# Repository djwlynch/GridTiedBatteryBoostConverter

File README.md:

# GridTiedBatteryBoostConverter

This is a project to build a device that will allow a 28 Cell 100AH LiFePo4 Battery Pack
to be connected to a generic MPPT Grid Tied Inverter via the solar DC input.
It will limit the power drawn from the battery pack to a maximum of 1000W.
This should allow a good base load for a typical 1st world house.
The LiFePo4 cell is 3.2V nominal voltage and 3.65V Max. 3.1V is fairly flat,so
this means the 28 cell battery pack voltage range should be 86.8V min 89.6V Nominal and 102.2V Max.
The majority of Grid tied inverters I have seen won't start until they get 150V DC from Pannels,
so this device will boost this voltage up to 160V.  It will include a current sense transformer and
isolating transformer to sample the house Voltage and current Draw, and thus be able to determine the
houses power consumption from the Grid.  It will be able to sense the power that it is supplying
to the Grid Tied inverter, and use this info to try to keep the house power from the Grid at about 0 Watts.
It will do this until it supplies a maximum of 1000W to the inverter, any higher than this and the grid
can supply it.  It will also have FETs for turning on and off a seperate charger.
The charger is 2000W 102.2V 20A. The CPU of the system is a Teensy_LC, with LCD, 3 buttons and a ESP_WROOM_02U
wifi module. The LCD is driven by an I2C bus the ESP has jumperable access to this bus also, and the I2C
bus is brought out to a header incase extra monitoring is required ie temperature or pressure etc.

The peak current mode control is based around the UCC2800 TI mosfet gate driver.

Warning I am not an electrical engineer and this may kill you / burn down your house,
all risks are your own.  I have not yet built this myself, but will update when I have.

<b>To install :</b>
change into your kicad projects directory and issue<br>
git clone https://github.com/djwlynch/GridTiedBatteryBoostConverter
Also in you kicad project directory issue the following<br>
git clone https://github.com/djwlynch/custom_kicad_library --recursive

the --recursive is important and it pulls down the required submodules for kicad librarys I have used,
namely teensy_library and teensy.pretty and digikey_kicad_library.

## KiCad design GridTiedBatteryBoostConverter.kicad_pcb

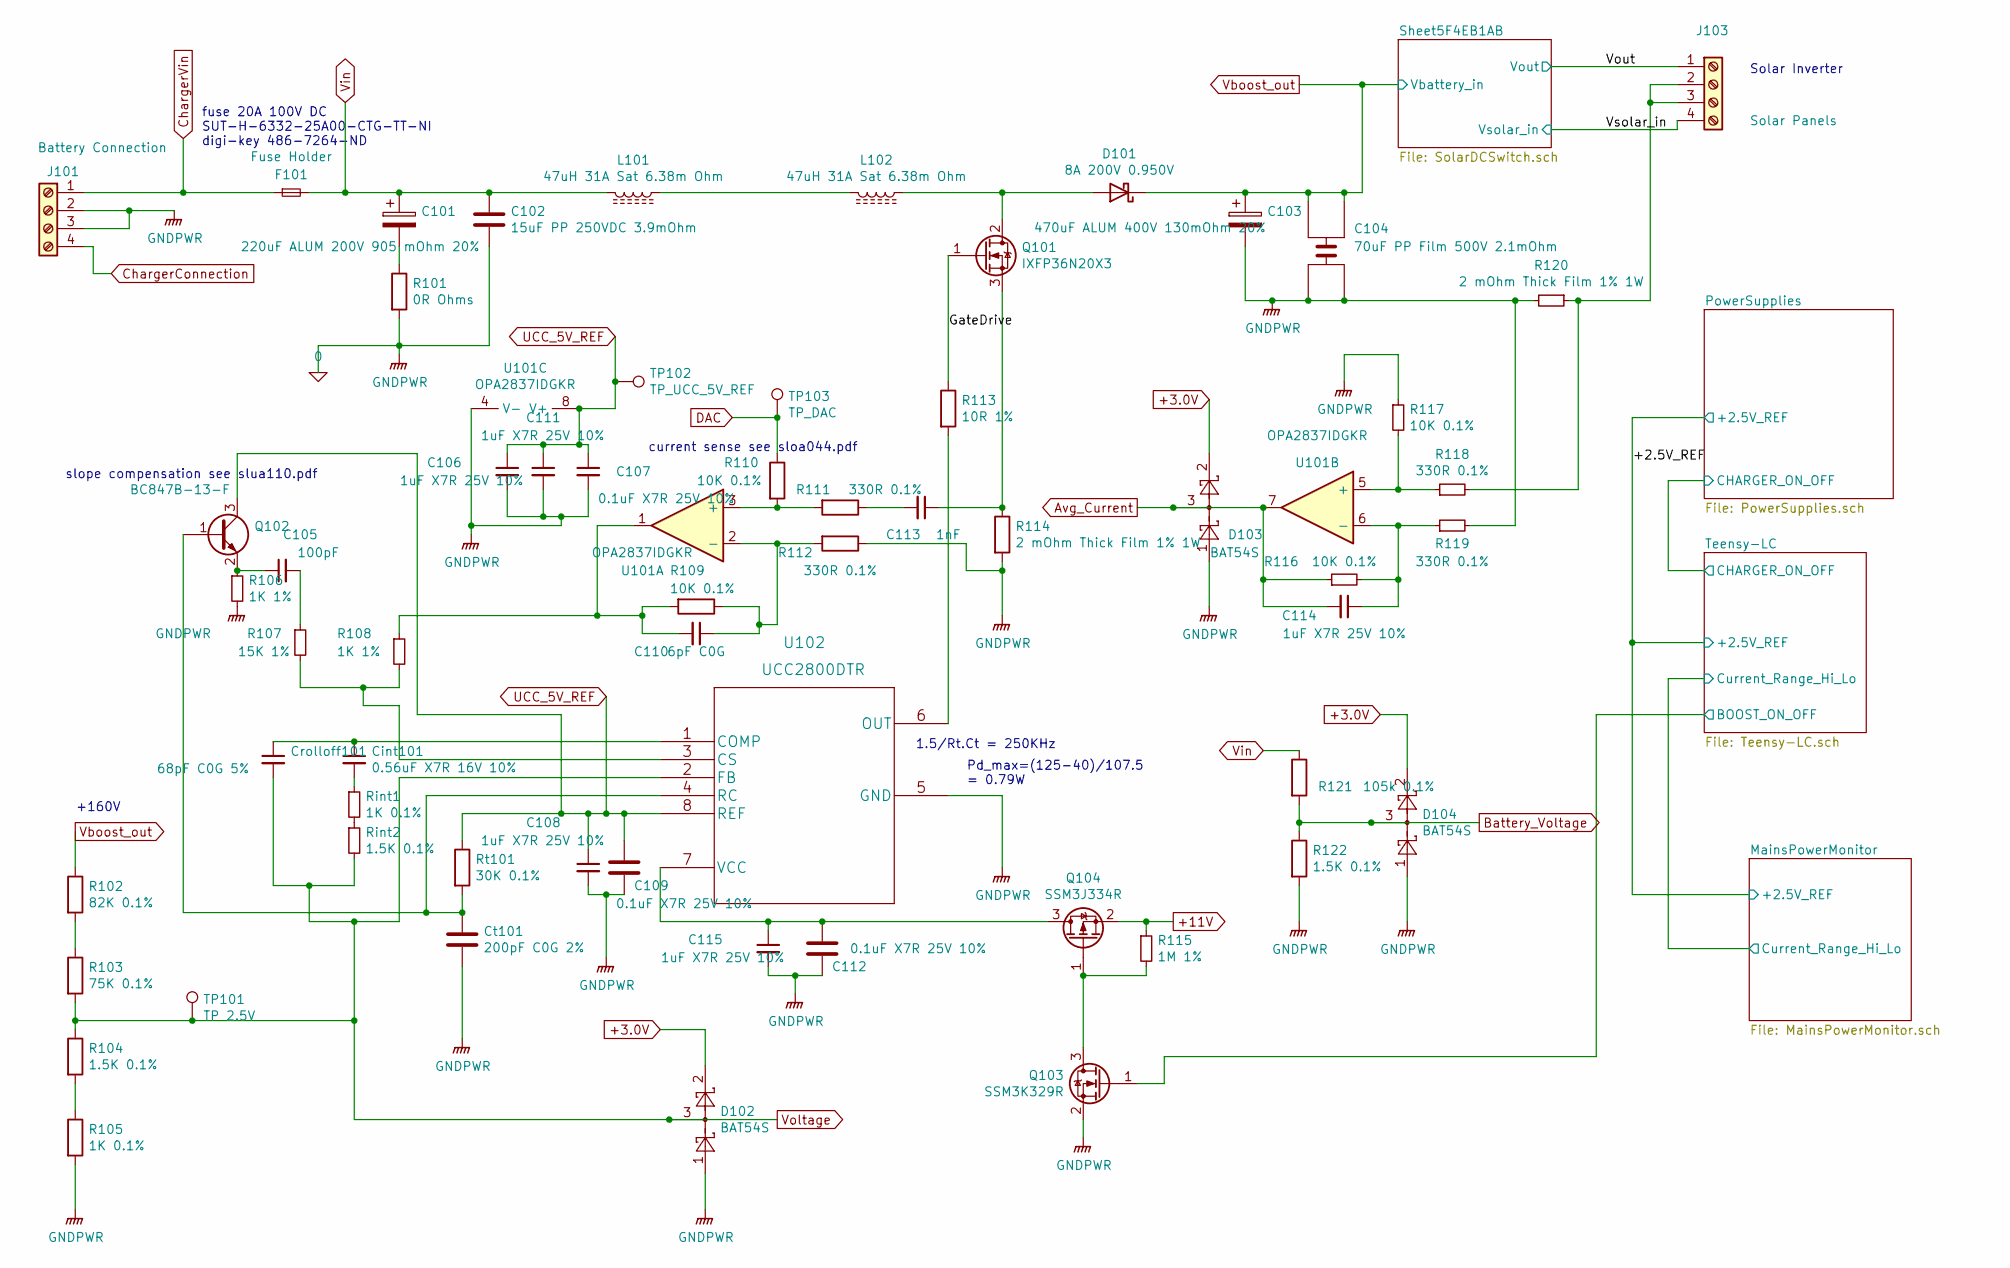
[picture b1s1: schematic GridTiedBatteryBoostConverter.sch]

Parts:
C101: 220uF ALUM 200V 905 mOhm 20%; CP_Radial_D22.0mm_P10.00mm_SnapIn; MPN SLP221M200A1P3
C102: 15uF PP 250VDC 3.9mOhm; C_Axial_44mm_24.5mm_P50mm; MPN C4GADUD5150AA1J
C103: 470uF ALUM 400V 130mOhm 20%; CP_Radial_D35.0mm_P10.00mm_SnapIn; MPN ELH477M400AT4AA
C104: 70uF PP Film 500V 2.1mOhm; C_RECT_4PIN_L42mm_W30mm_P37.5mm_P20.3mm; MPN C4AQLBW5700A3LK
C105: 100pF; C_0805_2012Metric_Pad1.15x1.40mm_HandSolder; MPN C0805C101JAGAC7800
C106, C108, C111, C114, C115: 1uF X7R 25V 10%; C_0805_2012Metric_Pad1.15x1.40mm_HandSolder; MPN 885012207078
C107, C109, C112: 0.1uF X7R 25V 10%; C_0805_2012Metric_Pad1.15x1.40mm_HandSolder; MPN CL21B104KACNNNC
C110: 6pF C0G; C_0805_2012Metric_Pad1.15x1.40mm_HandSolder; MPN CC0805CRNPO9BN6R0
C113: 1nF; C_0805_2012Metric_Pad1.15x1.40mm_HandSolder; MPN CC0805KRX7R9BB102
Cint101: 0.56uF X7R 16V 10%; C_0805_2012Metric_Pad1.15x1.40mm_HandSolder; MPN C0805C564K4RACTU
Crolloff101: 68pF C0G 5%; C_0805_2012Metric_Pad1.15x1.40mm_HandSolder; MPN 885012007081
Ct101: 200pF C0G 2%; C_0805_2012Metric_Pad1.15x1.40mm_HandSolder; MPN 08051A201GAT2A
D101: 8A 200V 0.950V; Diode_TO_220AC_Horizonal; MPN FES8DT-E3/45
D102, D103, D104: BAT54S; SOT-23_Handsoldering; MPN TBAT54S,LM
F101: Fuse Holder; BellFuse_6.3mmX32mm_FC_102-22; MPN FC-102-22
J101: Battery Connection; PhoenixContact_1x4_P5mm; MPN 1935792
J103: Solar Panels; TerminalBlock_4way_P6.35mm_P9.5mm_Holes1.7mm; MPN 1017516
L101, L102: 47uH 31A Sat 6.38m Ohm; Inductor_Wurth_7443763540470; MPN 7443763540470
Q101: IXFP36N20X3; TO-220_Horizontal_Offset_Drain; MPN IXFP36N20X3
Q102: BC847B-13-F; SOT-23_Handsoldering; MPN BC847B-13-F
Q103: SSM3K329R; SOT-23_Handsoldering; MPN SSM3K329R,LF
Q104: SSM3J334R; SOT-23_Handsoldering; MPN SSM3J334R,LF
R101: 0R Ohms; R_0805_2012Metric_Pad1.15x1.40mm_HandSolder; MPN RMCF0805ZT0R00
R102: 82K 0.1%; R_0805_2012Metric_Pad1.15x1.40mm_HandSolder; MPN ERA-6AEB823V
R103: 75K 0.1%; R_0805_2012Metric_Pad1.15x1.40mm_HandSolder; MPN ERJ-PB6B7502V
R104, R122: 1.5K 0.1%; R_0805_2012Metric_Pad1.15x1.40mm_HandSolder; MPN ERA-6AEB152V
R105: 1K 0.1%; R_0805_2012Metric_Pad1.15x1.40mm_HandSolder; MPN ERA-6AEB102V
R106, R108: 1K 1%; R_0805_2012Metric_Pad1.15x1.40mm_HandSolder; MPN RC0805FR-071KL
R107: 15K 1%; R_0805_2012Metric_Pad1.15x1.40mm_HandSolder; MPN CRGCQ0805F15K
R109, R110, R116, R117: 10K 0.1%; R_0805_2012Metric_Pad1.15x1.40mm_HandSolder; MPN ERA-6AEB103V
R111, R112, R118, R119: 330R 0.1%; R_0805_2012Metric_Pad1.15x1.40mm_HandSolder; MPN ERA-6AEB331V
R113: 10R 1%; R_0805_2012Metric_Pad1.15x1.40mm_HandSolder; MPN RC0805FR-0710RL
R114, R120: 2 mOhm Thick Film 1% 1W; R_1210_3225Metric_Pad1.42x2.65mm_HandSolder; MPN PMR25HZPFV2L00
R115: 1M 1%; R_0805_2012Metric_Pad1.15x1.40mm_HandSolder; MPN RC0805FR-071ML
R121: 105k 0.1%; R_0805_2012Metric_Pad1.15x1.40mm_HandSolder; MPN ERA-6AEB1053V
Rint1: 1K 0.1%; R_0805_2012Metric_Pad1.15x1.40mm_HandSolder; MPN ERA-6AEB102V
Rint2: 1.5K 0.1%; R_0805_2012Metric_Pad1.15x1.40mm_HandSolder; MPN ERA-6AEB152V
Rt101: 30K 0.1%; R_0805_2012Metric_Pad1.15x1.40mm_HandSolder; MPN ERA-6AEB303V
TP101: TP 2.5V; TestPoint_Pad_3.0x3.0mm
TP102: TP_UCC_5V_REF; TestPoint_Pad_3.0x3.0mm
TP103: TP_DAC; TestPoint_Pad_3.0x3.0mm
U101: OPA2837IDGKR; VSSOP-8_3.0x3.0mm_P0.65mm; MPN OPA2837IDGKR
U102: UCC2800DTR; SOIC-8_3.9x4.9mm_Pitch1.27mm; MPN UCC2800DTR

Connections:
0: C102.2, C103.2, C104.2, C104.3, C106.2, C107.2, C108.2, C109.2, C111.2, C112.2, C115.2, Ct101.2, D102.1, D103.1, D104.1, J101.2, J101.3, Q103.2 (S), R101.2, R105.2, R106.2, R112.1, R114.2, R117.1, R119.2, R120.2, R122.2, U101.4 (V-), U102.5 (GND); also elsewhere on the board
+3.0V: D102.2, D103.2, D104.2; also elsewhere on the board
+11V: Q104.2 (S), R115.1; also elsewhere on the board
/GateDrive: Q101.1 (G), R113.1
/Teensy-LC/BOOST_ON_OFF: Q103.1 (G); also elsewhere on the board
/Vout: J103.1; also elsewhere on the board
/Vsolar_in: J103.4; also elsewhere on the board
Avg_Current: C114.2, D103.3, R116.1, U101.7; also elsewhere on the board
Battery_Voltage: D104.3, R121.2, R122.1; also elsewhere on the board
ChargerConnection: J101.4; also elsewhere on the board
ChargerVin: F101.1, J101.1; also elsewhere on the board
DAC: R110.1, TP103.1; also elsewhere on the board
unnamed: C101.2, R101.1
unnamed: C105.1, Q102.2 (E), R106.1
unnamed: C105.2, R107.1
unnamed: C110.1, R109.1, R112.2, U101.2 (-)
unnamed: C110.2, R108.1, R109.2, U101.1
unnamed: C112.1, C115.1, Q104.3 (D), U102.7 (VCC)
unnamed: C113.1, Q101.3 (S), R114.1
unnamed: C113.2, R111.1
unnamed: C114.1, R116.2, R119.1, U101.6 (-)
unnamed: Cint101.1, Crolloff101.1, U102.1 (COMP)
unnamed: Cint101.2, Rint1.1
unnamed: Ct101.1, Q102.1 (B), Rt101.2, U102.4 (RC)
unnamed: D101.2 (A), L102.1, Q101.2 (D)
unnamed: J103.2, J103.3, R118.2, R120.1
unnamed: L101.1, L102.2
unnamed: Q103.3 (D), Q104.1 (G), R115.2
unnamed: R102.2, R103.1
unnamed: R104.2, R105.1
unnamed: R107.2, R108.2, U102.3 (CS)
unnamed: R110.2, R111.2, U101.3 (+)
unnamed: R113.2, U102.6 (OUT)
unnamed: R117.2, R118.1, U101.5 (+)
unnamed: Rint1.2, Rint2.1
UCC_5V_REF: C106.1, C107.1, C108.1, C109.1, C111.1, Q102.3 (C), Rt101.1, TP102.1, U101.8 (V+), U102.8 (REF)
Vboost_out: C103.1, C104.1, C104.4, D101.1 (K), R102.1; also elsewhere on the board
Vin: C101.1, C102.1, F101.2, L101.2, R121.1; also elsewhere on the board
Voltage: Crolloff101.2, D102.3, R103.2, R104.1, Rint2.2, TP101.1, U102.2 (FB); also elsewhere on the board

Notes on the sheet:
1.5/Rt.Ct = 250KHz
current sense see sloa044.pdf
slope compensation see slua110.pdf
Solar Inverter
Pd_max=(125-40)/107.5 = 0.79W
+160V
fuse 20A 100V DC SUT-H-6332-25A00-CTG-TT-NI digi-key 486-7264-ND

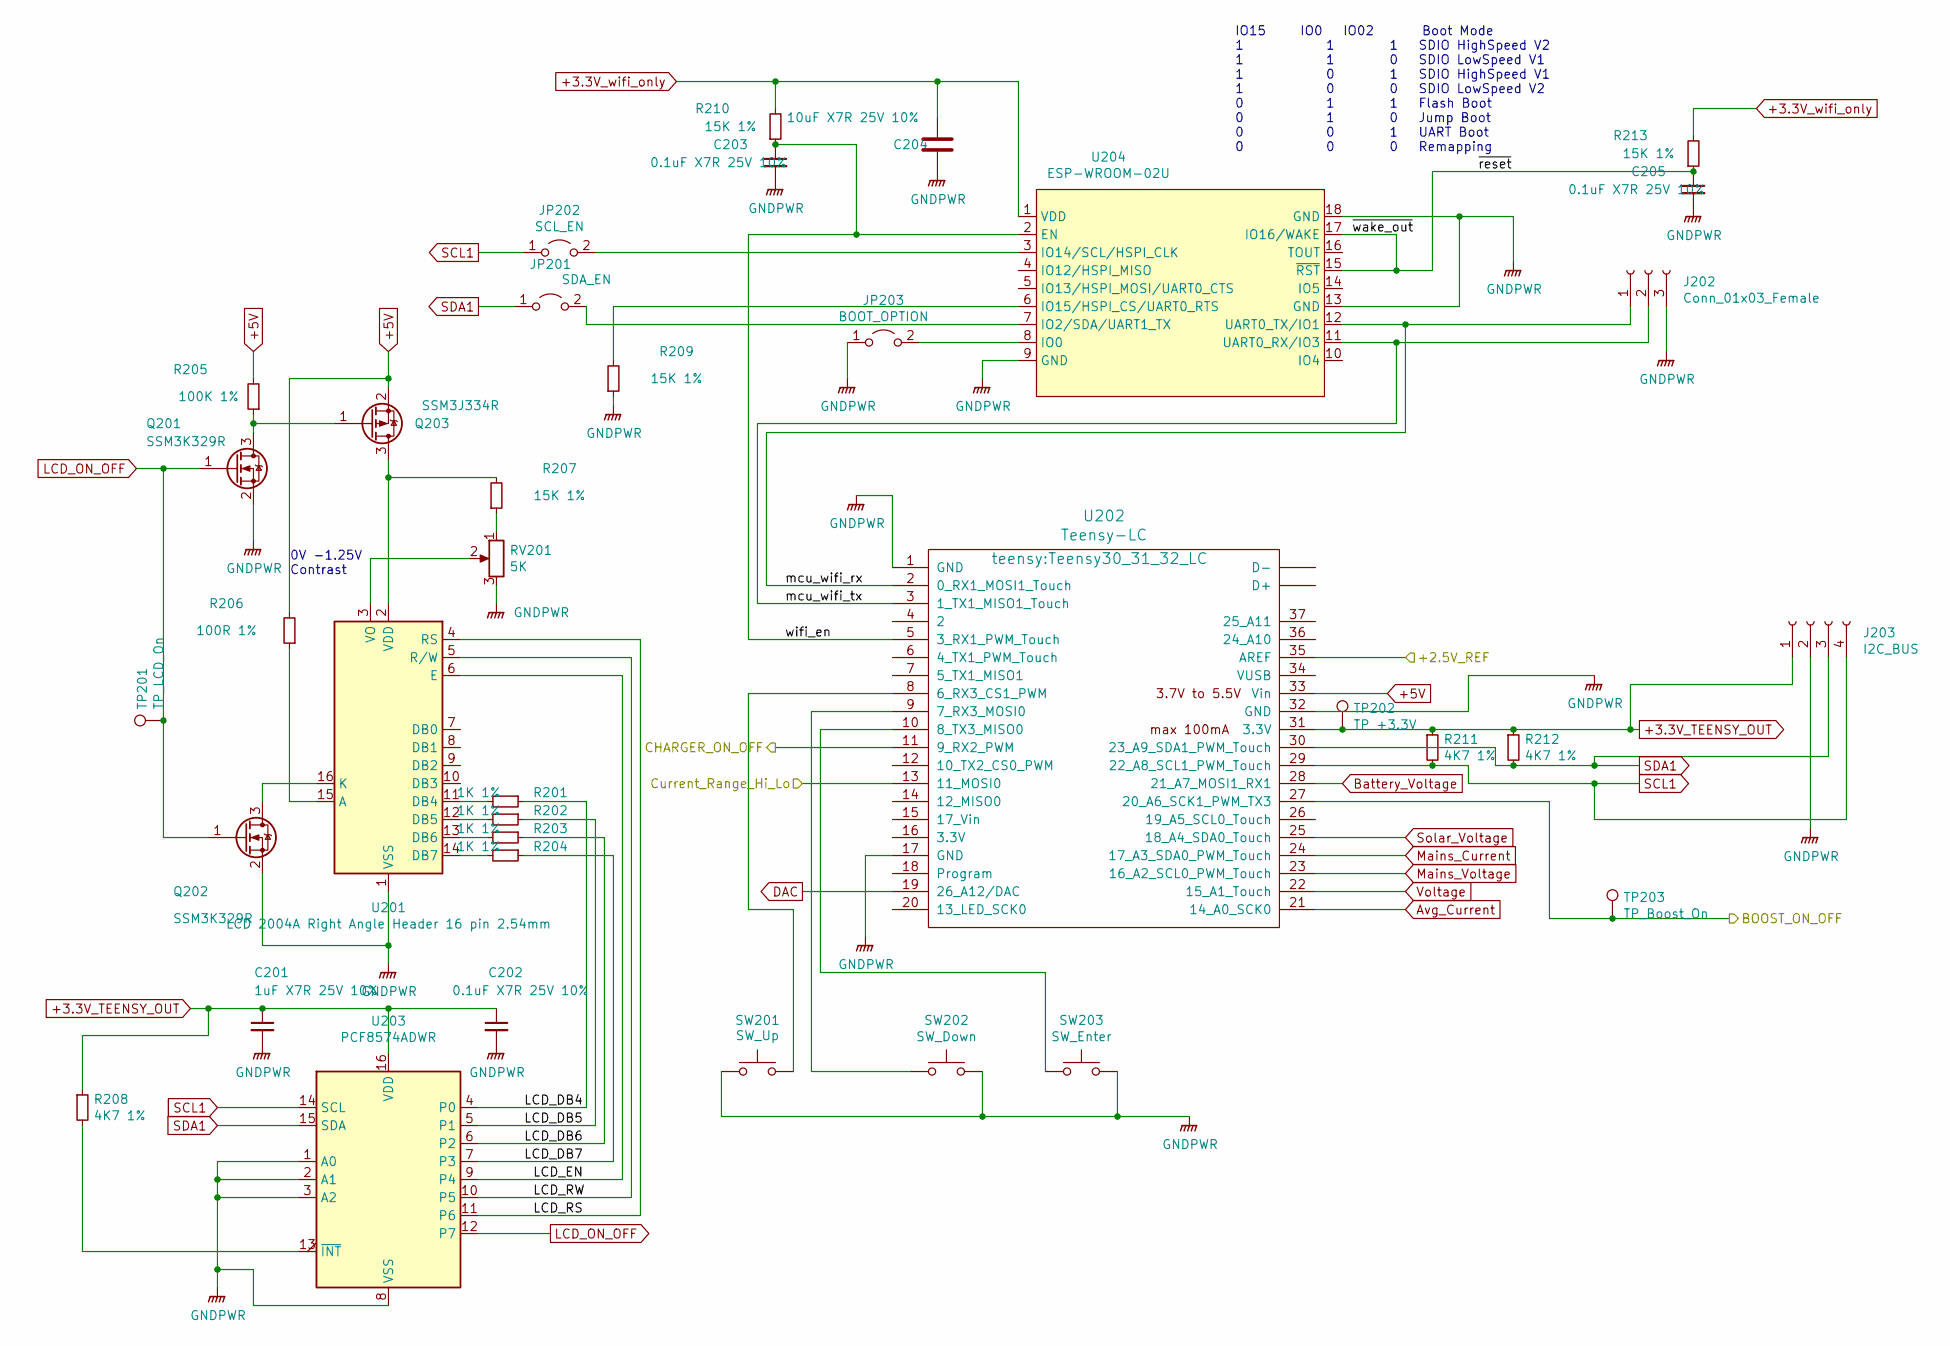
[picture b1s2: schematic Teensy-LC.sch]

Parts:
C201: 1uF X7R 25V 10%; C_0805_2012Metric_Pad1.15x1.40mm_HandSolder; MPN 885012207078
C202, C203, C205: 0.1uF X7R 25V 10%; C_0805_2012Metric_Pad1.15x1.40mm_HandSolder; MPN CL21B104KACNNNC
C204: 10uF X7R 25V 10%; C_1206_3216Metric_Pad1.42x1.75mm_HandSolder; MPN CL31B106KAHNNNE
J202: Conn_01x03_Female; Pin_Header_Straight_1x03_Pitch2.54mm; MPN PREC003SAAN-RC
J203: I2C_BUS; Pin_Header_Straight_1x04_Pitch2.54mm; MPN PH1-04-UA
JP201: SDA_EN; Pin_Header_Straight_1x02_Pitch2.54mm; MPN PREC002SAAN-RC
JP202: SCL_EN; Pin_Header_Straight_1x02_Pitch2.54mm; MPN PREC002SAAN-RC
JP203: BOOT_OPTION; Pin_Header_Straight_1x02_Pitch2.54mm; MPN PREC002SAAN-RC
Q201, Q202: SSM3K329R; SOT-23_Handsoldering; MPN SSM3K329R,LF
Q203: SSM3J334R; SOT-23_Handsoldering; MPN SSM3J334R,LF
R201, R202, R203, R204: 1K 1%; R_0805_2012Metric_Pad1.15x1.40mm_HandSolder; MPN RC0805FR-071KL
R205: 100K 1%; R_0805_2012Metric_Pad1.15x1.40mm_HandSolder; MPN RC0805FR-07100KL
R206: 100R 1%; R_0805_2012Metric_Pad1.15x1.40mm_HandSolder; MPN RC0805FR-07100RL
R207, R209, R210, R213: 15K 1%; R_0805_2012Metric_Pad1.15x1.40mm_HandSolder; MPN CRGCQ0805F15K
R208, R211, R212: 4K7 1%; R_0805_2012Metric_Pad1.15x1.40mm_HandSolder; MPN RC0805FR-074K7L
RV201: 5K; Potentiometer_Trimmer_Bourns_3006P; MPN 3006P-7-502LF
SW201: SW_Up; SW_Tactile_SPST_Angled_FSM104; MPN FSM104
SW202: SW_Down; SW_Tactile_SPST_Angled_FSM104; MPN FSM104
SW203: SW_Enter; SW_Tactile_SPST_Angled_FSM104; MPN FSM104
TP201: TP_LCD_On; TestPoint_Pad_3.0x3.0mm
TP202: TP +3.3V; TestPoint_Pad_3.0x3.0mm
TP203: TP_Boost_On; TestPoint_Pad_3.0x3.0mm
U201: LCD 2004A Right Angle Header 16 pin 2.54mm; LCD2004_Pin_Header_Angled_1x16_Pitch2.54mm; MPN PH1RB-16-UA
U202: Teensy-LC; Teensy30_31_32_LC; MPN DEV-13305
U203: PCF8574ADWR; SOIC-16W_7.5x10.3mm_Pitch1.27mm; MPN PCF8574ADWR
U204: ESP-WROOM-02U; MODULE_ESP-WROOM-02U; MPN ESP-WROOM-02U

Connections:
0: C201.2, C202.2, C203.2, C204.2, C205.2, J202.3, J203.2, JP203.1 (A), Q201.2 (S), Q202.2 (S), R209.1, RV201.3, SW201.1, SW202.2, SW203.2, U201.1 (VSS), U202.1 (GND), U202.17 (GND), U202.32 (GND), U203.1 (A0), U203.2 (A1), U203.3 (A2), U203.8 (VSS), U204.9 (GND), U204.13 (GND), U204.18 (GND), U204.19 (GND); also elsewhere on the board
+3.3V_TEENSY_OUT: C201.1, C202.1, J203.1, R208.1, R211.1, R212.1, TP202.1, U202.31 (3.3V), U203.16 (VDD)
+3.3V_wifi_only: C204.1, R210.2, R213.2, U204.1 (VDD); also elsewhere on the board
+5V: Q203.2 (S), R205.2, R206.2, U202.33 (Vin); also elsewhere on the board
/+2.5V_REF: U202.35 (AREF); also elsewhere on the board
/MainsPowerMonitor/Current_Range_Hi_Lo: U202.13 (11_MOSI0); also elsewhere on the board
/PowerSupplies/CHARGER_ON_OFF: U202.11 (9_RX2_PWM); also elsewhere on the board
/Teensy-LC/BOOST_ON_OFF: TP203.1, U202.27 (20_A6_SCK1_PWM_TX3); also elsewhere on the board
/Teensy-LC/LCD_DB4: R201.1, U203.4 (P0)
/Teensy-LC/LCD_DB5: R202.1, U203.5 (P1)
/Teensy-LC/LCD_DB6: R203.1, U203.6 (P2)
/Teensy-LC/LCD_DB7: R204.1, U203.7 (P3)
/Teensy-LC/LCD_EN: U201.6 (E), U203.9 (P4)
/Teensy-LC/LCD_RS: U201.4 (RS), U203.11 (P6)
/Teensy-LC/LCD_RW: U201.5 (R/W), U203.10 (P5)
/Teensy-LC/mcu_wifi_rx: J202.1, U202.2 (0_RX1_MOSI1_Touch), U204.12 (UART0_TX/IO1)
/Teensy-LC/mcu_wifi_tx: J202.2, U202.3 (1_TX1_MISO1_Touch), U204.11 (UART0_RX/IO3)
/Teensy-LC/wifi_en: C203.1, R210.1, U202.5 (3_RX1_PWM_Touch), U204.2 (EN)
/Teensy-LC/~reset: C205.1, R213.1, U204.15 (~RST), U204.17 (IO16/WAKE)
Avg_Current: U202.21 (14_A0_SCK0); also elsewhere on the board
Battery_Voltage: U202.28 (21_A7_MOSI1_RX1); also elsewhere on the board
DAC: U202.19 (26_A12/DAC); also elsewhere on the board
LCD_ON_OFF: Q201.1 (G), Q202.1 (G), TP201.1, U203.12 (P7)
Mains_Current: U202.24 (17_A3_SDA0_PWM_Touch); also elsewhere on the board
Mains_Voltage: U202.23 (16_A2_SCL0_PWM_Touch); also elsewhere on the board
unnamed: JP201.2 (B), U204.7 (IO2/SDA/UART1_TX)
unnamed: JP202.2 (B), U204.3 (IO14/SCL/HSPI_CLK)
unnamed: JP203.2 (B), U204.8 (IO0)
unnamed: Q201.3 (D), Q203.1 (G), R205.1
unnamed: Q202.3 (D), U201.16 (K)
unnamed: Q203.3 (D), R207.2, U201.2 (VDD)
unnamed: R201.2, U201.11 (DB4)
unnamed: R202.2, U201.12 (DB5)
unnamed: R203.2, U201.13 (DB6)
unnamed: R204.2, U201.14 (DB7)
unnamed: R206.1, U201.15 (A)
unnamed: R207.1, RV201.1
unnamed: R208.2, U203.13 (~INT~)
unnamed: R209.2, U204.6 (IO15/HSPI_CS/UART0_RTS)
unnamed: RV201.2, U201.3 (VO)
unnamed: SW201.2, U202.8 (6_RX3_CS1_PWM)
unnamed: SW202.1, U202.9 (7_RX3_MOSI0)
unnamed: SW203.1, U202.10 (8_TX3_MISO0)
SCL1: J203.4, JP202.1 (A), R211.2, U202.29 (22_A8_SCL1_PWM_Touch), U203.14 (SCL)
SDA1: J203.3, JP201.1 (A), R212.2, U202.30 (23_A9_SDA1_PWM_Touch), U203.15 (SDA)
Solar_Voltage: U202.25 (18_A4_SDA0_Touch); also elsewhere on the board
Voltage: U202.22 (15_A1_Touch); also elsewhere on the board

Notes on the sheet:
0V -1.25V Contrast
IO15 IO0 IO02 Boot Mode 1 1 1 SDIO HighSpeed V2 1 1 0 SDIO LowSpeed V1 1 0 1 SDIO HighSpeed V1 1 0 0 SDIO LowSpeed V2 0 1 1 Flash Boot 0 1 0 Jump Boot 0 0 1 UART Boot 0 0 0 Remapping

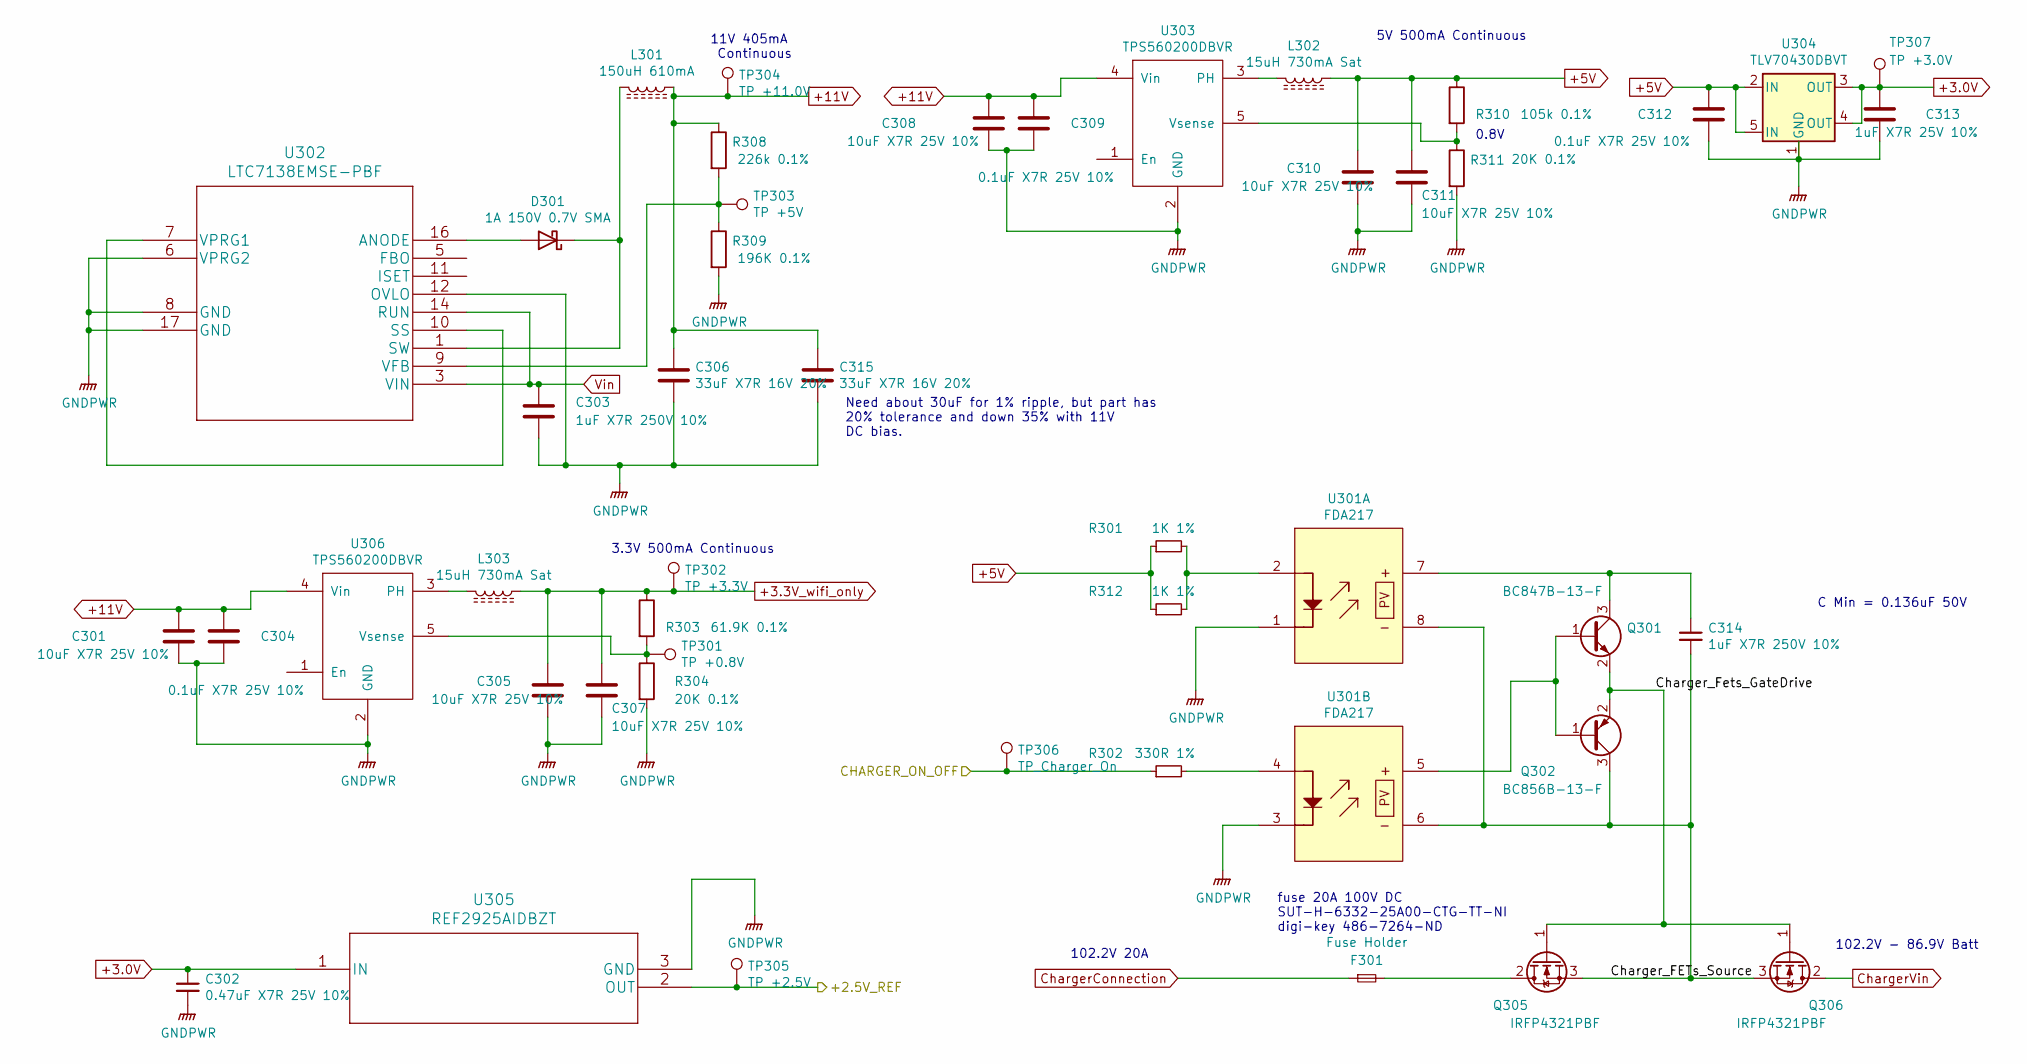
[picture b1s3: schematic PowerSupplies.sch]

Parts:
C301, C305, C307, C308, C310, C311: 10uF X7R 25V 10%; C_1206_3216Metric_Pad1.42x1.75mm_HandSolder; MPN CL31B106KAHNNNE
C302: 0.47uF X7R 25V 10%; C_0805_2012Metric_Pad1.15x1.40mm_HandSolder; MPN CL21B474KAFNNNE
C303, C314: 1uF X7R 250V 10%; C_2220_5650Metric_Pad1.97x5.40mm_HandSolder; MPN C5750X7R2E105K230KA
C304, C309, C312: 0.1uF X7R 25V 10%; C_0805_2012Metric_Pad1.15x1.40mm_HandSolder; MPN CL21B104KACNNNC
C306, C315: 33uF X7R 16V 20%; C_1812_4532Metric_Pad1.30x3.40mm_HandSolder; MPN C4532X7R1C336M250KC
C313: 1uF X7R 25V 10%; C_0805_2012Metric_Pad1.15x1.40mm_HandSolder; MPN 885012207078
D301: 1A 150V 0.7V SMA; D_SMA_Handsoldering; MPN SBR1U150SA-13
F301: Fuse Holder; BellFuse_6.3mmX32mm_FC_102-22; MPN FC-102-22
L301: 150uH 610mA; Inductor_Bourns_PM3308; MPN PM3308-151M-RC
L302, L303: 15uH 730mA Sat; Inductor_1210_HandSoldering; MPN CBC3225T150KR
Q301: BC847B-13-F; SOT-23_Handsoldering; MPN BC847B-13-F
Q302: BC856B-13-F; SOT-23_Handsoldering; MPN BC856B-13-F
Q305, Q306: IRFP4321PBF; TO-247-3_Horizontal_TabDown; MPN IRFP4321PBF
R301, R312: 1K 1%; R_0805_2012Metric_Pad1.15x1.40mm_HandSolder; MPN RC0805FR-071KL
R302: 330R 1%; R_0805_2012Metric_Pad1.15x1.40mm_HandSolder; MPN CRGCQ0805F330R
R303: 61.9K 0.1%; R_0805_2012Metric_Pad1.15x1.40mm_HandSolder; MPN ERA-6AEB6192V
R304, R311: 20K 0.1%; R_0805_2012Metric_Pad1.15x1.40mm_HandSolder; MPN ERA-6AEB203V
R308: 226k 0.1%; R_0805_2012Metric_Pad1.15x1.40mm_HandSolder; MPN ERA-6AEB2263V
R309: 196K 0.1%; R_0805_2012Metric_Pad1.15x1.40mm_HandSolder; MPN ERA-6AEB1963V
R310: 105k 0.1%; R_0805_2012Metric_Pad1.15x1.40mm_HandSolder; MPN ERA-6AEB1053V
TP301: TP +0.8V; TestPoint_Pad_3.0x3.0mm
TP302: TP +3.3V; TestPoint_Pad_3.0x3.0mm
TP303: TP +5V; TestPoint_Pad_3.0x3.0mm
TP304: TP +11.0V; TestPoint_Pad_3.0x3.0mm
TP305: TP +2.5V; TestPoint_Pad_3.0x3.0mm
TP306: TP_Charger_On; TestPoint_Pad_3.0x3.0mm
TP307: TP +3.0V; TestPoint_Pad_3.0x3.0mm
U301: FDA217; DIP-8_SMD; MPN FDA217S
U302: LTC7138EMSE-PBF; MPN LTC7138EMSE#PBF
U303, U306: TPS560200DBVR; SOT-23-5_HandSoldering; MPN TPS560200DBVR
U304: TLV70430DBVT; SOT-23-5_HandSoldering; MPN TLV70430DBVT
U305: REF2925AIDBZT; SOT-23_Handsoldering; MPN REF2925AIDBZT

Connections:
0: C301.2, C302.2, C303.2, C304.2, C305.2, C306.2, C307.2, C308.2, C309.2, C310.2, C311.2, C312.2, C313.2, C315.2, R304.2, R309.2, R311.2, U301.1, U301.3, U302.6 (VPRG2), U302.8 (GND), U302.12 (OVLO), U302.17 (GND), U303.2 (GND), U304.1 (GND), U305.3 (GND), U306.2 (GND); also elsewhere on the board
+3.0V: C302.1, C313.1, TP307.1, U304.3 (OUT), U304.4 (OUT), U305.1 (IN); also elsewhere on the board
+3.3V_wifi_only: C305.1, C307.1, L303.1, R303.1, TP302.1; also elsewhere on the board
+5V: C310.1, C311.1, C312.1, L302.1, R301.1, R310.1, R312.1, U304.2 (IN), U304.5 (IN); also elsewhere on the board
+11V: C301.1, C304.1, C306.1, C308.1, C309.1, C315.1, L301.1, R308.1, TP304.1, U303.4 (Vin), U306.4 (Vin); also elsewhere on the board
/+2.5V_REF: TP305.1, U305.2 (OUT); also elsewhere on the board
/PowerSupplies/CHARGER_ON_OFF: R302.1, TP306.1; also elsewhere on the board
/PowerSupplies/Charger_FETs_Source: C314.2, Q302.3 (C), Q305.3 (S), Q306.3 (S), U301.6, U301.8
/PowerSupplies/Charger_Fets_GateDrive: Q301.2 (E), Q302.2 (E), Q305.1 (G), Q306.1 (G)
ChargerConnection: F301.1; also elsewhere on the board
ChargerVin: Q306.2 (D); also elsewhere on the board
unnamed: C314.1, Q301.3 (C), U301.7
unnamed: D301.1 (K), L301.2, U302.1 (SW)
unnamed: D301.2 (A), U302.16 (ANODE)
unnamed: F301.2, Q305.2 (D)
unnamed: L302.2, U303.3 (PH)
unnamed: L303.2, U306.3 (PH)
unnamed: Q301.1 (B), Q302.1 (B), U301.5
unnamed: R301.2, R312.2, U301.2
unnamed: R302.2, U301.4
unnamed: R303.2, R304.1, TP301.1, U306.5 (Vsense)
unnamed: R308.2, R309.1, TP303.1, U302.9 (VFB)
unnamed: R310.2, R311.1, U303.5 (Vsense)
unnamed: U302.7 (VPRG1), U302.10 (SS)
Vin: C303.1, U302.3 (VIN), U302.14 (RUN); also elsewhere on the board

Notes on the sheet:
0.8V
C Min = 0.136uF 50V
102.2V - 86.9V Batt
102.2V 20A
11V 405mA Continuous
5V 500mA Continuous
3.3V 500mA Continuous
Need about 30uF for 1% ripple, but part has 20% tolerance and down 35% with 11V DC bias.
fuse 20A 100V DC SUT-H-6332-25A00-CTG-TT-NI digi-key 486-7264-ND

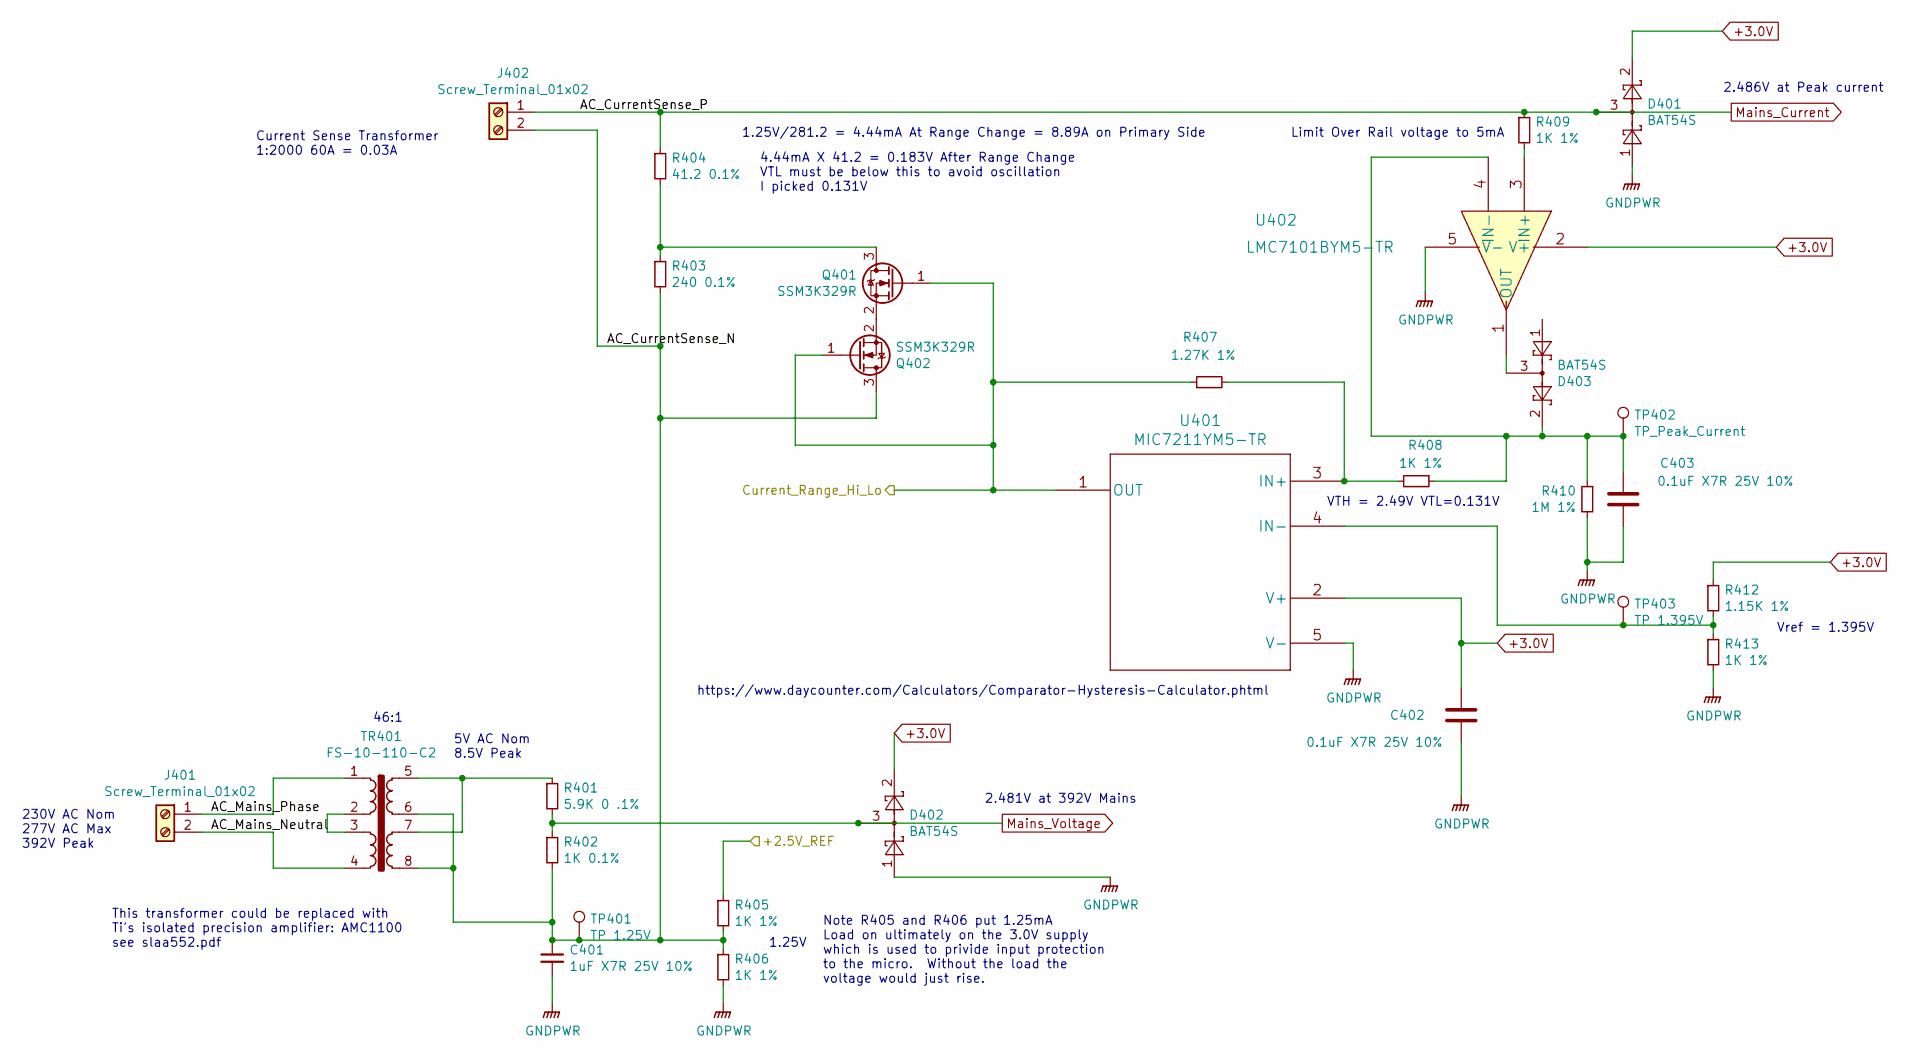
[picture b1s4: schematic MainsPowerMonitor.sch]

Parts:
C401: 1uF X7R 25V 10%; C_0805_2012Metric_Pad1.15x1.40mm_HandSolder; MPN 885012207078
C402, C403: 0.1uF X7R 25V 10%; C_0805_2012Metric_Pad1.15x1.40mm_HandSolder; MPN CL21B104KACNNNC
D401, D402, D403: BAT54S; SOT-23_Handsoldering; MPN TBAT54S,LM
J401, J402: Screw_Terminal_01x02; Term_Block_1x2_P5mm; MPN 1792863
Q401, Q402: SSM3K329R; SOT-23_Handsoldering; MPN SSM3K329R,LF
R401: 5.9K 0 .1%; R_0805_2012Metric_Pad1.15x1.40mm_HandSolder; MPN ERA-6AEB5901V
R402: 1K 0.1%; R_0805_2012Metric_Pad1.15x1.40mm_HandSolder; MPN ERA-6AEB102V
R403: 240 0.1%; R_0805_2012Metric_Pad1.15x1.40mm_HandSolder; MPN ERA-6AEB241V
R404: 41.2 0.1%; R_0805_2012Metric_Pad1.15x1.40mm_HandSolder; MPN 8-1625868-6
R405, R406, R408, R409, R413: 1K 1%; R_0805_2012Metric_Pad1.15x1.40mm_HandSolder; MPN RC0805FR-071KL
R407: 1.27K 1%; R_0805_2012Metric_Pad1.15x1.40mm_HandSolder; MPN RC0805FR-071K27L
R410: 1M 1%; R_0805_2012Metric_Pad1.15x1.40mm_HandSolder; MPN RC0805FR-071ML
R412: 1.15K 1%; R_0805_2012Metric_Pad1.15x1.40mm_HandSolder; MPN RC0805FR-071K15L
TP401: TP 1.25V; TestPoint_Pad_3.0x3.0mm
TP402: TP_Peak_Current; TestPoint_Pad_3.0x3.0mm
TP403: TP 1.395V; TestPoint_Pad_3.0x3.0mm
TR401: FS-10-110-C2; FS10-110-C2; MPN FS10-110-C2
U401: MIC7211YM5-TR; SOT-23-5_HandSoldering; MPN MIC7211YM5-TR
U402: LMC7101BYM5-TR; SOT-23-5_HandSoldering; MPN LMC7101BYM5-TR

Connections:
0: C401.2, C402.2, C403.2, D401.1, D402.1, R406.2, R410.2, R413.2, U401.5 (V-), U402.5 (V-); also elsewhere on the board
+3.0V: C402.1, D401.2, D402.2, R412.1, U401.2 (V+), U402.2 (V+); also elsewhere on the board
/+2.5V_REF: R405.1; also elsewhere on the board
/MainsPowerMonitor/AC_CurrentSense_N: C401.1, J402.2, Q402.3 (D), R402.2, R403.2, R405.2, R406.1, TP401.1, TR401.6, TR401.8
/MainsPowerMonitor/AC_Mains_Neutral: J401.2, TR401.4
/MainsPowerMonitor/AC_Mains_Phase: J401.1, TR401.1
/MainsPowerMonitor/Current_Range_Hi_Lo: Q401.1 (G), Q402.1 (G), R407.1, U401.1 (OUT); also elsewhere on the board
Mains_Current: D401.3, J402.1, R404.1, R409.1; also elsewhere on the board
Mains_Voltage: D402.3, R401.2, R402.1; also elsewhere on the board
unnamed: C403.1, D403.2, R408.1, R410.1, TP402.1, U402.4 (IN-)
unnamed: D403.3, U402.1 (OUT)
unnamed: Q401.2 (S), Q402.2 (S)
unnamed: Q401.3 (D), R403.1, R404.2
unnamed: R401.1, TR401.5, TR401.7
unnamed: R407.2, R408.2, U401.3 (IN+)
unnamed: R409.2, U402.3 (IN+)
unnamed: R412.2, R413.1, TP403.1, U401.4 (IN-)
unnamed: TR401.2, TR401.3

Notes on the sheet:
230V AC Nom 277V AC Max 392V Peak
5V AC Nom 8.5V Peak
1.25V
Current Sense Transformer 1:2000 60A = 0.03A
2.486V at Peak current
2.481V at 392V Mains
46:1
This transformer could be replaced with Ti's isolated precision amplifier: AMC1100 see slaa552.pdf
Note R405 and R406 put 1.25mA Load on ultimately on the 3.0V supply which is used to privide input protection to the micro. Without the load the voltage would just rise.
Vref = 1.395V
https://www.daycounter.com/Calculators/Comparator-Hysteresis-Calculator.phtml
VTH = 2.49V VTL=0.131V
Limit Over Rail voltage to 5mA
1.25V/281.2 = 4.44mA At Range Change = 8.89A on Primary Side
4.44mA X 41.2 = 0.183V After Range Change VTL must be below this to avoid oscillation I picked 0.131V

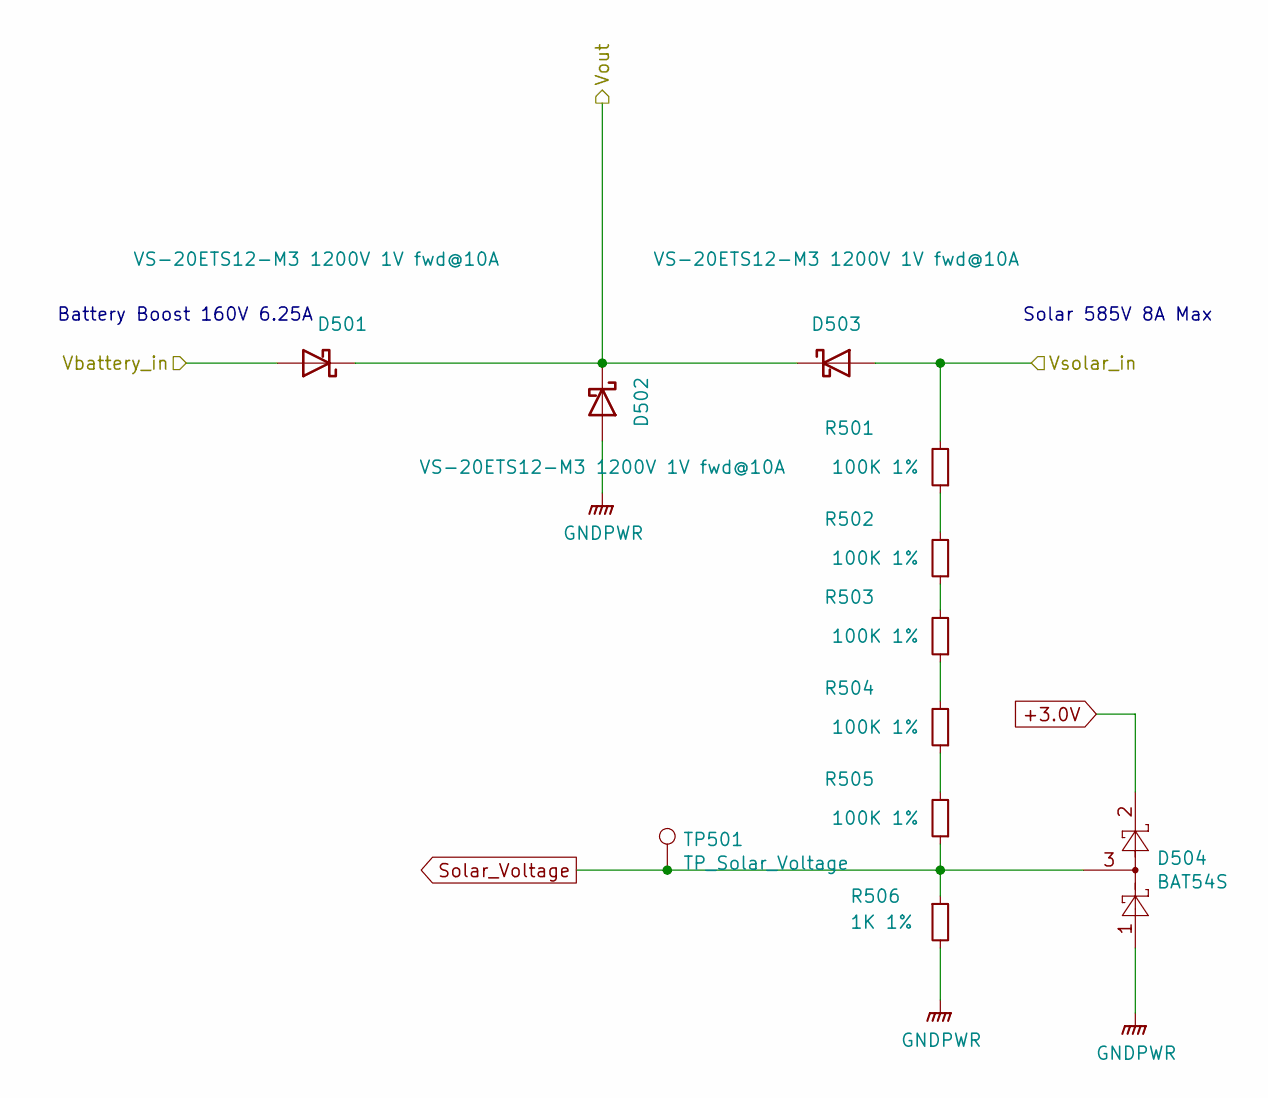
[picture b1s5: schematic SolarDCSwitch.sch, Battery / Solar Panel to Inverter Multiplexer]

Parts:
D501, D502, D503: VS-20ETS12-M3 1200V 1V fwd@10A; Diode_TO_220AC_Horizonal; MPN VS-20ETS12-M3
D504: BAT54S; SOT-23_Handsoldering; MPN TBAT54S,LM
R501, R502, R503, R504, R505: 100K 1%; R_0805_2012Metric_Pad1.15x1.40mm_HandSolder; MPN RC0805FR-07100KL
R506: 1K 1%; R_0805_2012Metric_Pad1.15x1.40mm_HandSolder; MPN RC0805FR-071KL
TP501: TP_Solar_Voltage; TestPoint_Pad_3.0x3.0mm

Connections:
0: D502.2 (A), D504.1, R506.2; also elsewhere on the board
+3.0V: D504.2; also elsewhere on the board
/Vout: D501.1 (K), D502.1 (K), D503.1 (K); also elsewhere on the board
/Vsolar_in: D503.2 (A), R501.2; also elsewhere on the board
unnamed: R501.1, R502.2
unnamed: R502.1, R503.2
unnamed: R503.1, R504.2
unnamed: R504.1, R505.2
Solar_Voltage: D504.3, R505.1, R506.1, TP501.1; also elsewhere on the board
Vboost_out: D501.2 (A); also elsewhere on the board

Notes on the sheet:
Solar 585V 8A Max
Battery Boost 160V 6.25A

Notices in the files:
parts and their libraries:
Copyright 2016 Accelerated Designs. All rights reserved.
